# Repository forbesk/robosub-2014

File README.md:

robosub-2014
============

#Configuration

###Virtual Environment
The following steps below will setup the python virtual environment.

```bash
virtualenv env
source env/bin/activate
pip install -r requirements.txt
```

###Setting up Dashboard
The dashboard has several dependencies that need to be installed before it can be used.

__development__
```bash
pushd src/auvweb/dashboard
bower install
npm install
popd
```

__production__
```bash
pushd src/auvweb/dashboard
bower install -p
popd
```

###Development Server
Once your virtual environment has been configured and the Dashboard has its required
dependencies the following command will run the auvweb server. AUVWeb should now be running on port `5000`.

__development__
```bash
bin/auvweb
```

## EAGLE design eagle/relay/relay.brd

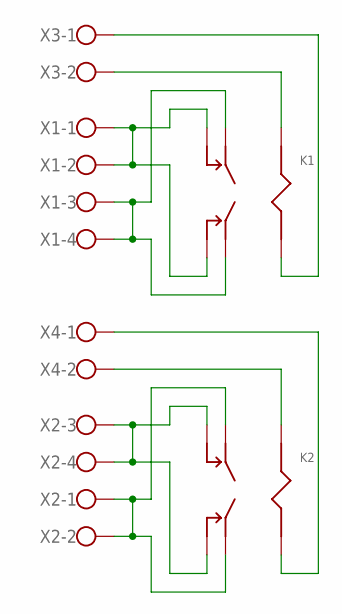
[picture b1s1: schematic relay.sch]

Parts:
K1, K2: T92S7D12; T92-PCPIN
X1, X2: W237-4
X3, X4: W237-102

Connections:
unnamed: K1.2A (2), K1.2B (2), K1.6A (6), K1.6B (6), X1.1, X1.2
unnamed: K1.4A (4), K1.4B (4), K1.8A (8), K1.8B (8), X1.3, X1.4
unnamed: K1.0A (0), K1.0B (0), X3.2
unnamed: K1.1A (1), K1.1B (1), X3.1
unnamed: K2.2A (2), K2.2B (2), K2.6A (6), K2.6B (6), X2.3, X2.4
unnamed: K2.4A (4), K2.4B (4), K2.8A (8), K2.8B (8), X2.1, X2.2
unnamed: K2.0A (0), K2.0B (0), X4.2
unnamed: K2.1A (1), K2.1B (1), X4.1

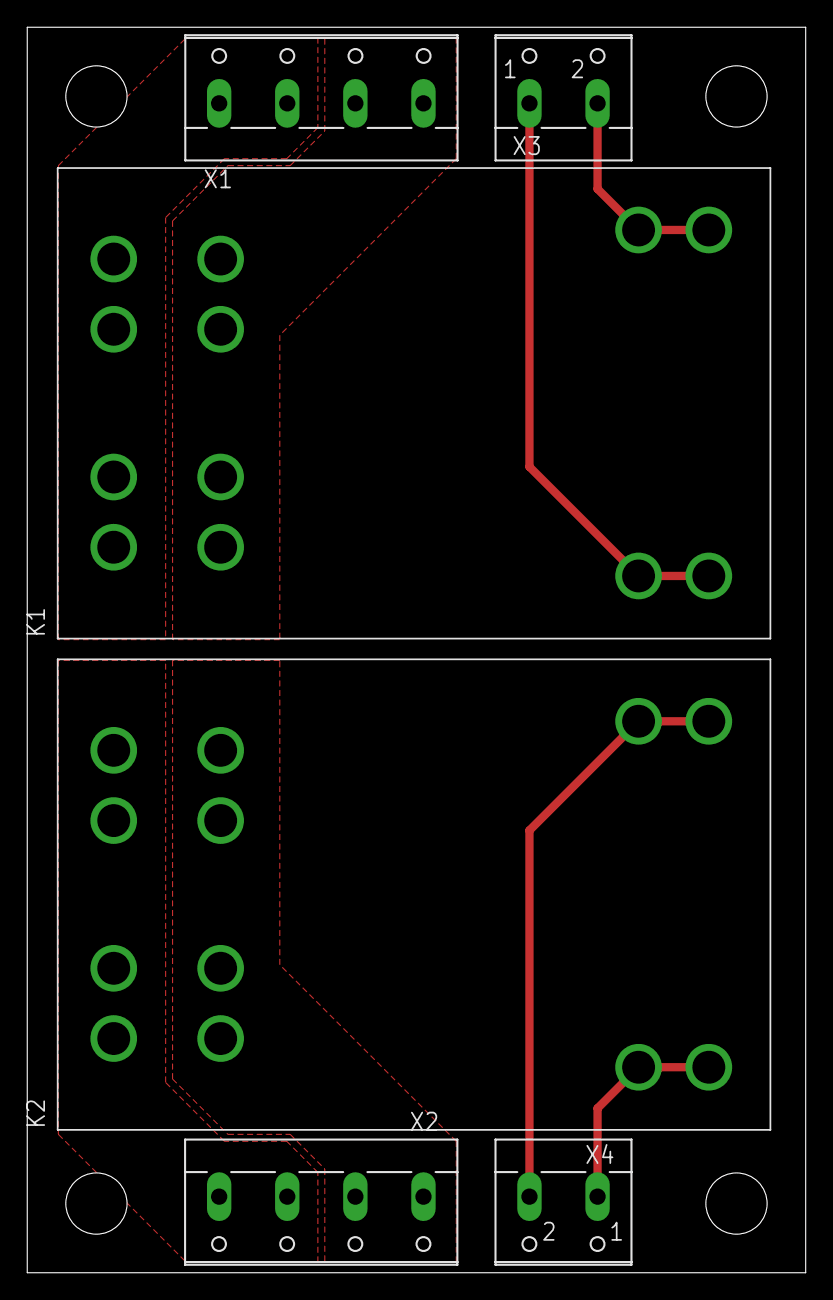
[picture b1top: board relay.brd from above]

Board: 2 copper layers, 57.1 x 91.4 mm, 6 parts (0 on the bottom side), 8 nets.

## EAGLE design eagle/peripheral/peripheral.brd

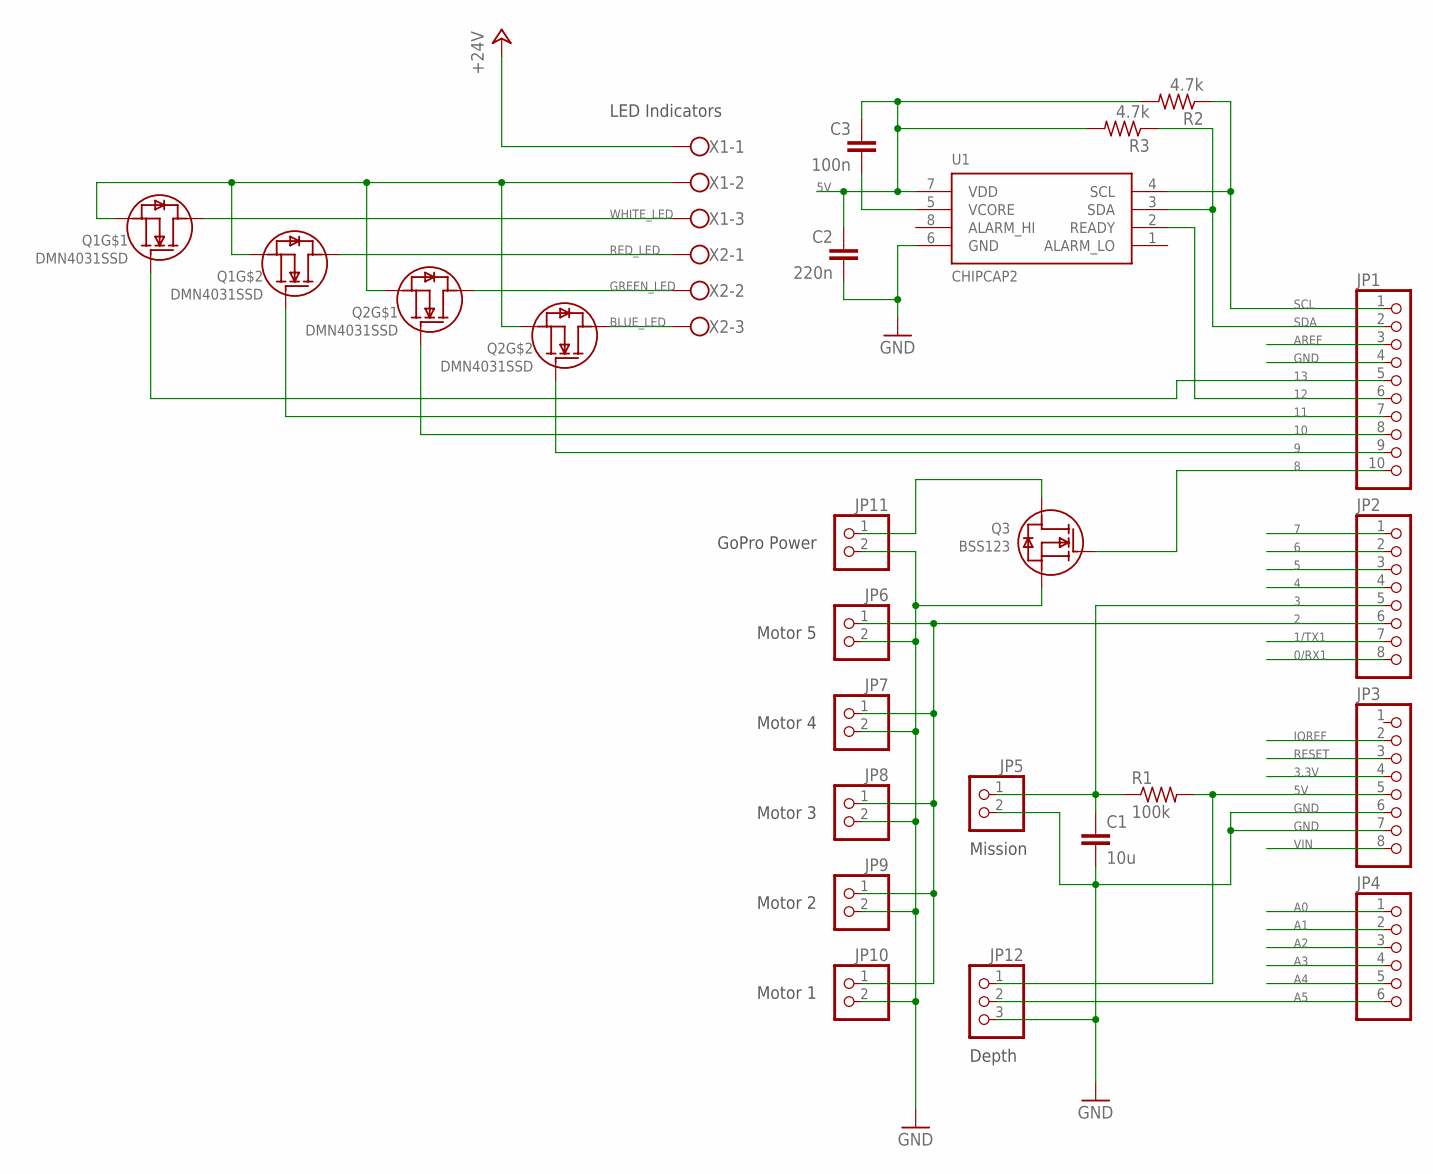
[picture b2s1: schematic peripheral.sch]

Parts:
C1: 10u; C0805K
C2: 220n; C0603
C3: 100n; C0603
JP1: PINHD-1X10; 1X10
JP2, JP3: PINHD-1X8; 1X08
JP4: PINHD-1X6; 1X06
JP5, JP6, JP7, JP8, JP9, JP10, JP11: PINHD-1X2; 1X02
JP12: PINHD-1X3; 1X03
Q1, Q2: DMN4031SSD; SO-8
Q3: BSS123; SOT-23
R1: 100k; R0805
R2, R3: 4.7k; R0603
U1: CHIPCAP2
X1, X2: W237-103

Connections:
0/RX1: JP2.8
1/TX1: JP2.7
2: JP2.6, JP6.1, JP7.1, JP8.1, JP9.1, JP10.1
3: C1.1, JP2.5, JP5.1, R1.1
3.3V: JP3.4
4: JP2.4
5: JP2.3
5V: C2.1, C3.1, JP3.5, JP12.1, R1.2, R2.2, R3.2, U1.7 (VDD)
6: JP2.2
7: JP2.1
8: JP1.10, Q3.1 (G)
9: JP1.9, Q2.2 (G)
10: JP1.8, Q2.4 (G)
11: JP1.7, Q1.2 (G)
12: JP1.6, U1.2 (READY)
13: JP1.5, Q1.4 (G)
+24V: X1.1
A0: JP4.1
A1: JP4.2
A2: JP4.3
A3: JP4.4
A4: JP4.5
A5: JP4.6, JP12.2
AREF: JP1.3
BLUE_LED: Q2.7 (D), Q2.8 (D), X2.3
GND: C1.2, C2.2, JP1.4, JP3.6, JP3.7, JP5.2, JP6.2, JP7.2, JP8.2, JP9.2, JP10.2, JP11.2, JP12.3, Q3.3 (S), U1.6 (GND)
GREEN_LED: Q2.5 (D), Q2.6 (D), X2.2
IOREF: JP3.2
unnamed: JP11.1, Q3.2 (D)
unnamed: C3.2, U1.5 (VCORE)
unnamed: Q1.1 (S), Q1.3 (S), Q2.1 (S), Q2.3 (S), X1.2
RED_LED: Q1.7 (D), Q1.8 (D), X2.1
RESET: JP3.3
SCL: JP1.1, R2.1, U1.4 (SCL)
SDA: JP1.2, R3.1, U1.3 (SDA)
VIN: JP3.8
WHITE_LED: Q1.5 (D), Q1.6 (D), X1.3

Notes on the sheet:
Motor 1
Motor 2
Motor 3
Motor 4
Motor 5
GoPro Power
Mission
Depth
LED Indicators

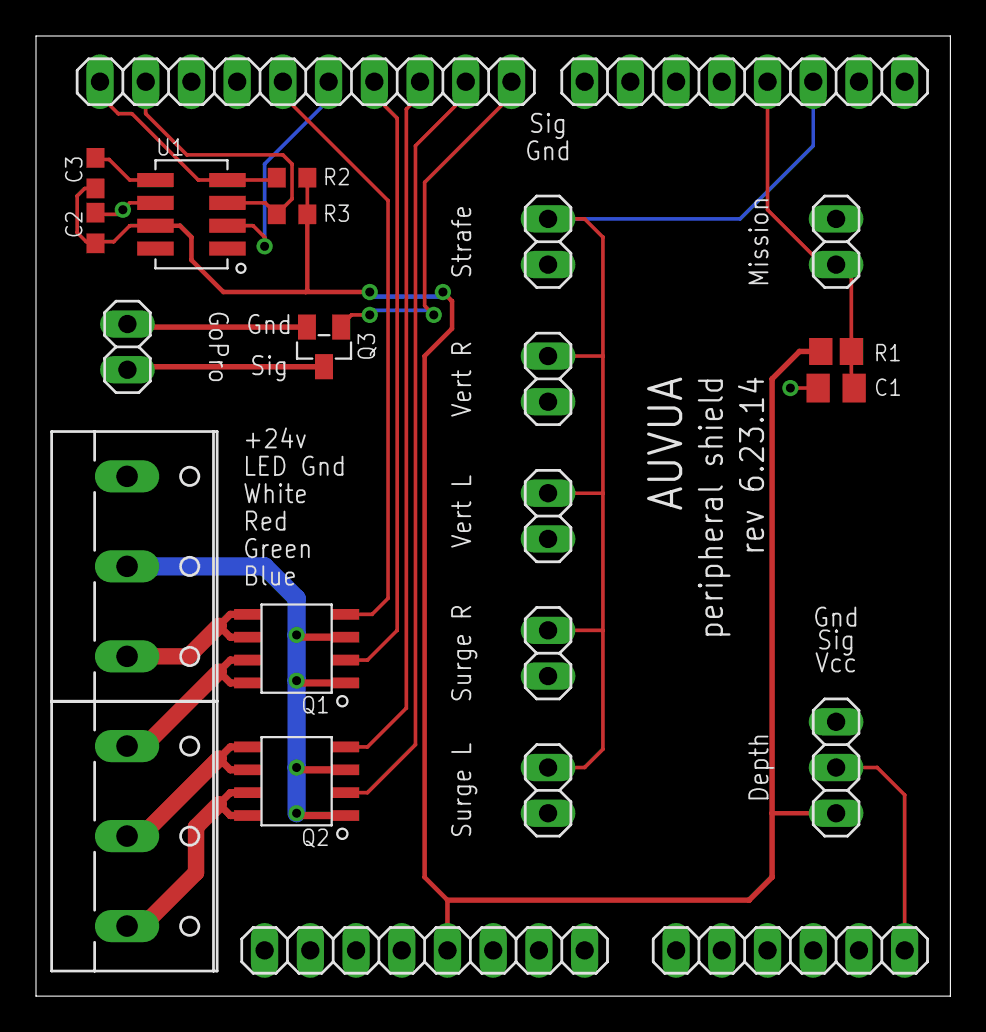
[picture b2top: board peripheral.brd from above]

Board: 2 copper layers, 50.8 x 53.3 mm, 24 parts (0 on the bottom side), 20 nets.

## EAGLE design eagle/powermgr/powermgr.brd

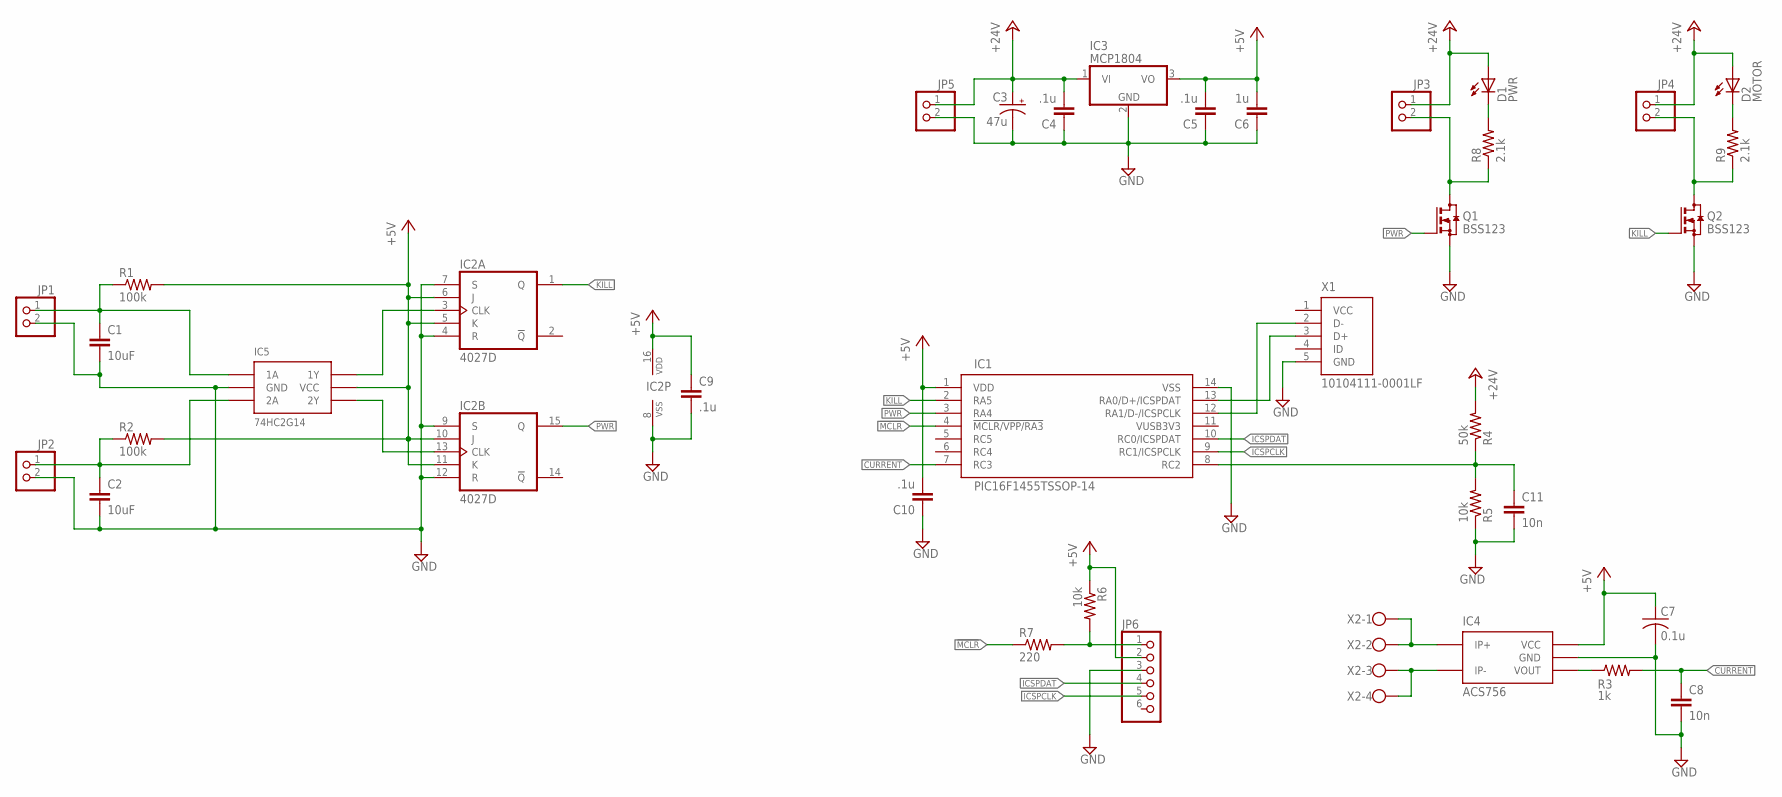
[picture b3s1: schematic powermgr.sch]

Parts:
C1, C2: 10uF; C0805
C3: 47u; E2,5-6
C4, C5: .1u; C0805
C6: 1u; C0805
C7: 0.1u; C1206K
C8, C11: 10n; C0603K
C9, C10: .1u; C0603K
D1: PWR; CHIP-LED0805
D2: MOTOR; CHIP-LED0805
IC1: PIC16F1455TSSOP-14; TSSOP-14
IC2: 4027D; SO16
IC3: MCP1804; SOT223
IC4: ACS756; 5PFF
IC5: 74HC2G14; TSSOP-6
JP1, JP2, JP3, JP4, JP5: PINHD-1X2; 1X02
JP6: PINHD-1X6; 1X06
Q1, Q2: BSS123; SOT23
R1, R2: 100k; R0805
R3: 1k; R0603
R4: 50k; R0603
R5, R6: 10k; R0603
R7: 220; R0603
R8, R9: 2.1k; R0805
X1: 10104111-0001LF; USBAB
X2: W237-4

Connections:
!MCLR: IC1.4 (!MCLR/VPP/RA3), R7.1
+5V: C5.2, C6.2, C7.1, C9.1, C10.2, IC1.1 (VDD), IC2.5 (K), IC2.6 (J), IC2.10 (J), IC2.11 (K), IC2.16 (VDD), IC3.3 (VO), IC4.1 (VCC), IC5.5 (VCC), JP6.2, R1.2, R2.2, R6.1
+24V: C3.+, C4.2, D1.A, D2.A, IC3.1 (VI), JP3.1, JP4.1, JP5.1, R4.2
CURRENT: C8.1, IC1.7 (RC3), R3.2
GND: C1.2, C2.2, C3.-, C4.1, C5.1, C6.1, C7.2, C8.2, C9.2, C10.1, C11.2, IC1.14 (VSS), IC2.4 (R), IC2.7 (S), IC2.8 (VSS), IC2.9 (S), IC2.12 (R), IC3.2 (GND), IC4.2 (GND), IC5.2 (GND), JP1.2, JP2.2, JP5.2, JP6.3, Q1.2 (S), Q2.2 (S), R5.1, X1.5 (GND)
ICSPCLK: IC1.9 (RC1/ICSPCLK), JP6.5
ICSPDAT: IC1.10 (RC0/ICSPDAT), JP6.4
KILL: IC1.2 (RA5), IC2.1 (Q), Q2.1 (G)
unnamed: C1.1, IC5.1 (1A), JP1.1, R1.1
unnamed: JP3.2, Q1.3 (D), R8.1
unnamed: JP4.2, Q2.3 (D), R9.1
unnamed: IC4.4 (IP+), X2.1, X2.2
unnamed: IC4.5 (IP-), X2.3, X2.4
unnamed: D1.C, R8.2
unnamed: IC4.3 (VOUT), R3.1
unnamed: C11.1, IC1.8 (RC2), R4.1, R5.2
unnamed: JP6.1, R6.2, R7.2
unnamed: D2.C, R9.2
unnamed: C2.1, IC5.3 (2A), JP2.1, R2.1
unnamed: IC2.3 (CLK), IC5.6 (1Y)
unnamed: IC2.13 (CLK), IC5.4 (2Y)
PWR: IC1.3 (RA4), IC2.15 (Q), Q1.1 (G)
USBD+: IC1.13 (RA0/D+/ICSPDAT), X1.3 (D+)
USBD-: IC1.12 (RA1/D-/ICSPCLK), X1.2 (D-)

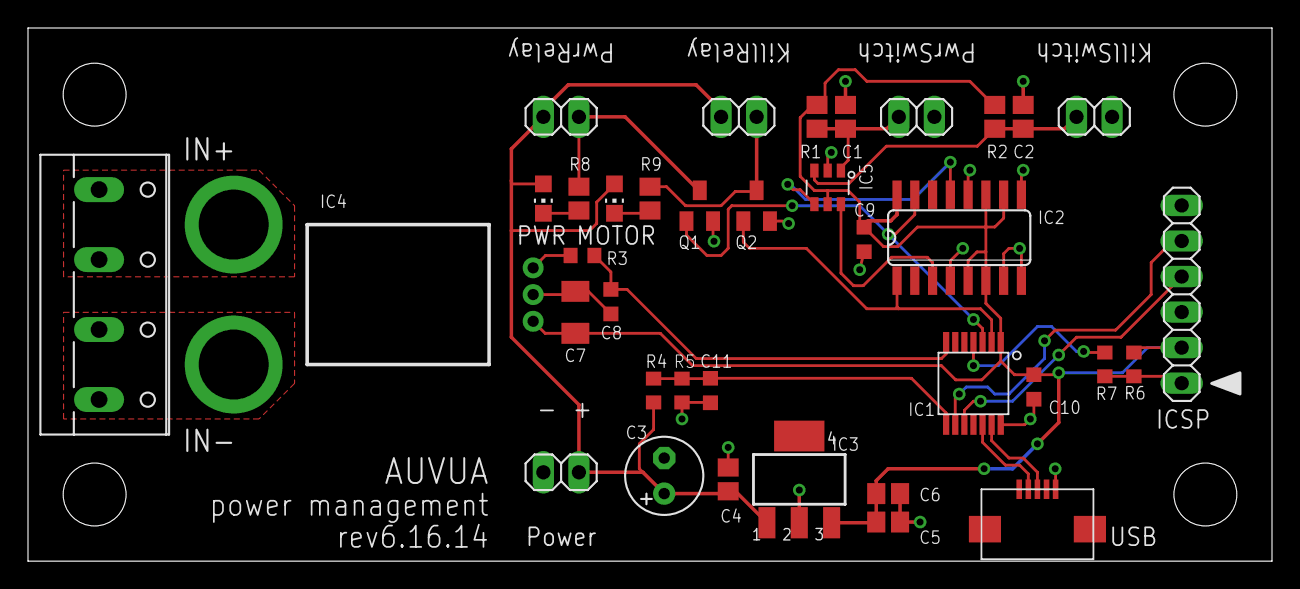
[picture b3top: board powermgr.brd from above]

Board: 2 copper layers, 88.9 x 38.1 mm, 37 parts (0 on the bottom side), 24 nets.

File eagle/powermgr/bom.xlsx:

Part | Description | Vendor | Vendor PN | Price | Quantity | Ext. Price | Notes
C1, C2 | SMD 0805 cap, 10uF | Digikey | 1276-2890-1-ND | 0.22 | 2 | 0.44
C3 | E2.5-6 polarized cap, 47uF | Digikey | 493-1106-ND | 0.28000000000000003 | 1 | 0.28000000000000003
C4, C5 | SMD 0805 cap, 0.1uF | Digikey | 1276-1003-1-ND | 0.1 | 2 | 0.2
C6 | SMD 0805 cap, 1.0uF | Digikey | 1276-1029-1-ND | 0.1 | 1 | 0.1
C7 | SMD 1206 cap, 0.1uF | Digikey | 1276-1017-1-ND | 0.1 | 1 | 0.1
C8, C11 | SMD 0603 cap, 10nF | Digikey | 1276-1921-1-ND | 0.1 | 2 | 0.2
C9, C10 | SMD 0603 cap, 0.1uF | Digikey | 1276-1857-1-ND | 0.1 | 1 | 0.1
R1, R2 | SMD 0805 res, 100k | Digikey | RMCF0805FT100KCT-ND | 0.04 | 2 | 0.08
R3 | SMD 0603 res, 1k | Digikey | RMCF0603JT1K00CT-ND | 0.02 | 1 | 0.02
R4 | SMD 0603 res, 50k | Digikey | RMCF0603JT51K0CT-ND | 0.02 | 1 | 0.02 | 51k available for $0.02, 50k is >$3
R5, R6 | SMD 0603 res, 10k | Digikey | RMCF0603JT10K0CT-ND | 0.02 | 2 | 0.04
R7 | SMD 0603 res, 220 | Digikey | RMCF0603JT220RCT-ND | 0.02 | 1 | 0.02
R8, R9 | SMD 0805 res, 2.1k | Digikey | RMCF0805FT2K10CT-ND | 0.04 | 2 | 0.08
D1, D2 | SMD 0805 green LED | Digikey | 732-4983-1-ND | 0.28999999999999998 | 2 | 0.57999999999999996
Q1, Q2 | SOT-23 N-MOSFET | Digikey | BSS123NCT-ND | 0.24 | 2 | 0.48
JP1, JP2, JP3, JP4, JP5 | 2-pin 0.1" lock header | Digikey | A1921-ND | 0.14000000000000001 | 5 | 0.70000000000000007
JP6 | 6-pin 0.1" header | Digikey | 609-3263-ND | 0.24 | 1 | 0.24
X1 | Micro-USB A/B | Digikey | 609-4053-1-ND | 0.79 | 1 | 0.79
X2 | 4-pin 5mm screw terminal | Digikey | A98357-ND | 2.71 | 1 | 2.71
IC1 | PIC16F micro controller | Digikey | PIC16F1455-I/ST-ND | 1.78 | 1 | 1.78
IC2 | 4027D dual JK flip-flop | Digikey | MC14027BDGOS-ND | 0.44 | 1 | 0.44
IC3 | 5v LDO regulator | Digikey | MCP1804T-5002I/DBCT-ND | 0.84 | 1 | 0.84
IC4 | 100A current transducer | Digikey | 620-1238-ND | 7.98 | 1 | 7.98
IC5 | Dual Schmitt Trigger | Digikey | 568-7739-1-ND | 0.52 | 1 | 0.52
 |  |  |  | Total: | 36 | 18.739999999999998

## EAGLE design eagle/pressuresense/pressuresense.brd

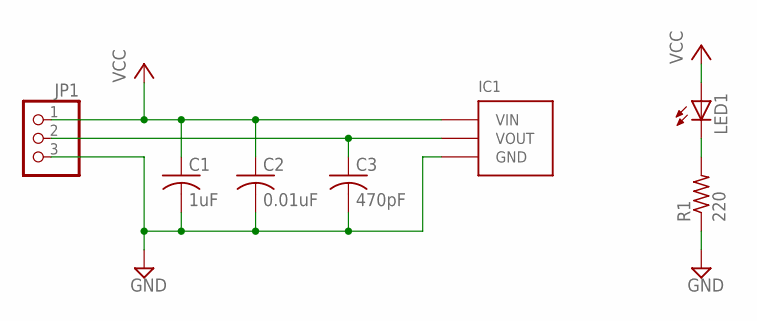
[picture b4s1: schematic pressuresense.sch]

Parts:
C1: 1uF; C0805K
C2: 0.01uF; C0805K
C3: 470pF; C0805K
IC1: MPXA4250AC6U
JP1: PINHD-1X3; 1X03
LED1: LEDCHIP-LED0805; CHIP-LED0805
R1: 220; R0805

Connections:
GND: C1.2, C2.2, C3.2, IC1.P$3 (GND), JP1.3, R1.1
unnamed: LED1.C, R1.2
VCC: C1.1, C2.1, IC1.P$2 (VIN), JP1.1, LED1.A
VOUT: C3.1, IC1.P$4 (VOUT), JP1.2

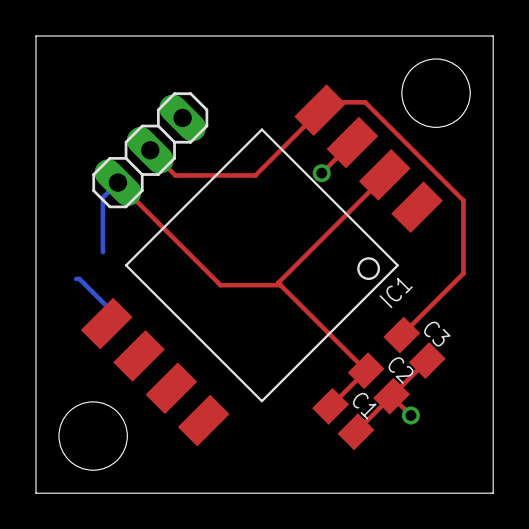
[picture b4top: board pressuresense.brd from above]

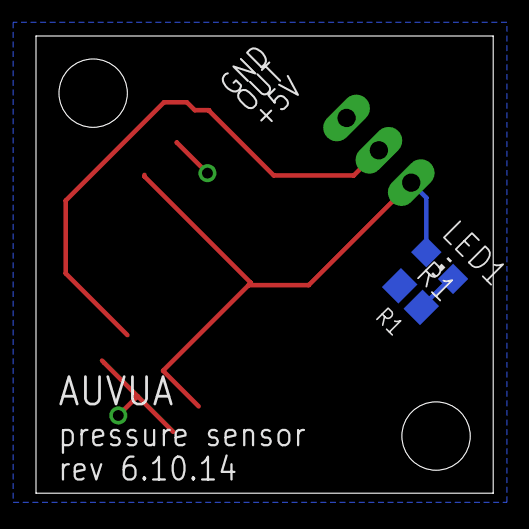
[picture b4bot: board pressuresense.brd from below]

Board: 2 copper layers, 25.4 x 25.4 mm, 7 parts (2 on the bottom side), 4 nets.

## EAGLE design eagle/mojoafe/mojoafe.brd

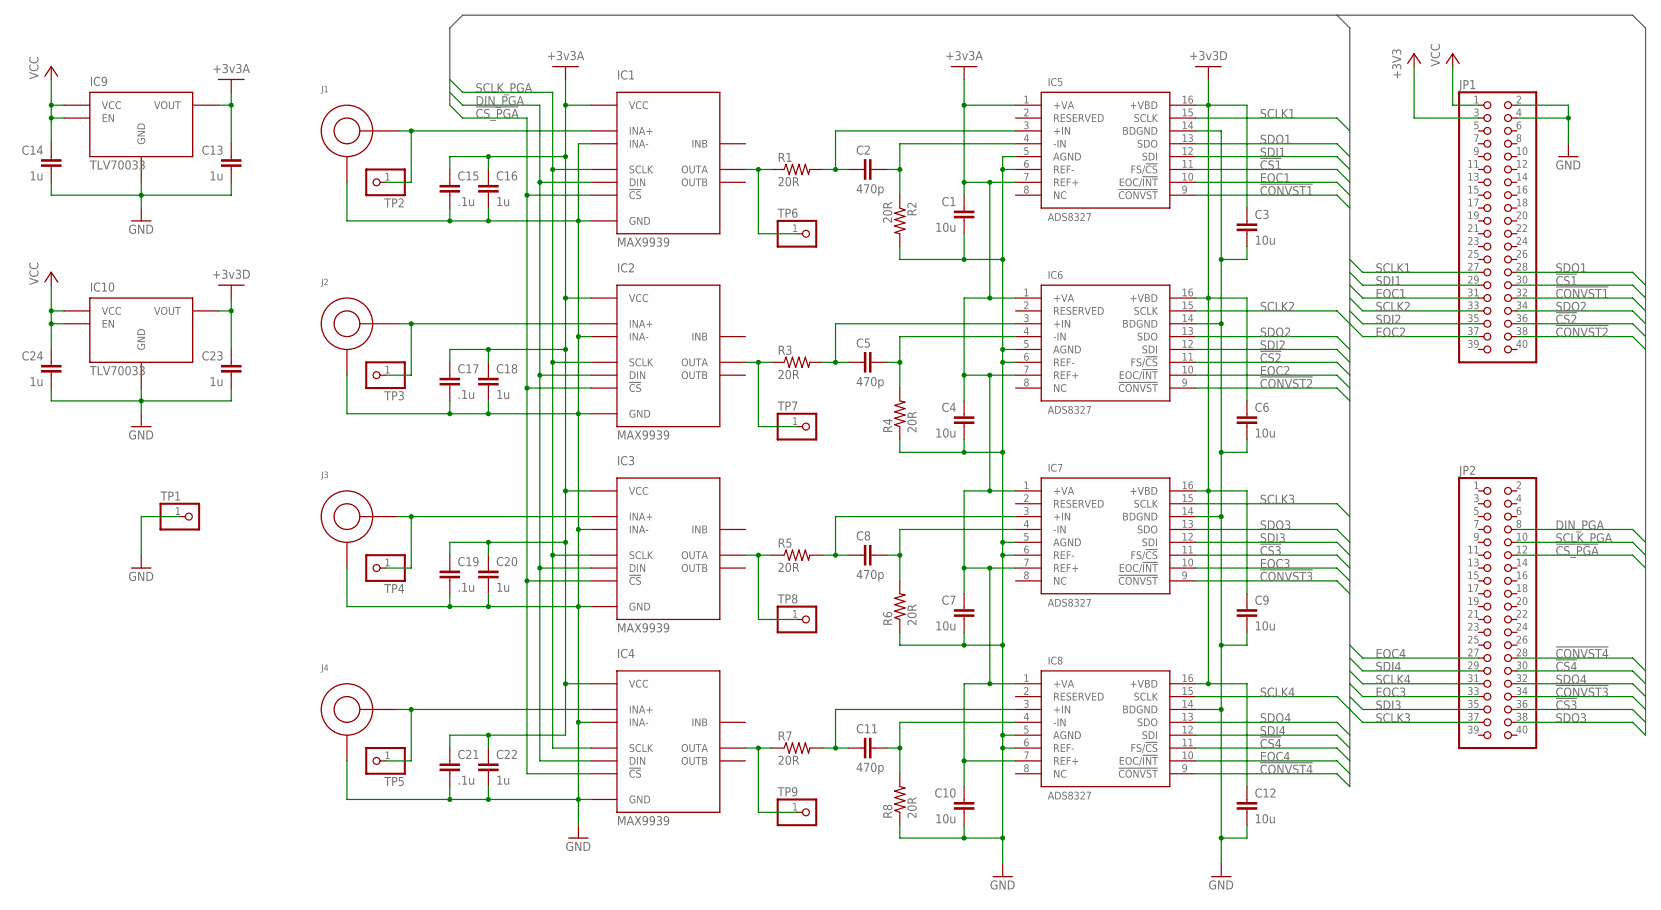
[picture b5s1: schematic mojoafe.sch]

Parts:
C1, C3, C4, C6, C7, C9, C10, C12: 10u; C0603K
C2, C5, C8, C11: 470p; C0603K
C13, C14, C16, C18, C20, C22, C23, C24: 1u; C0603K
C15, C17, C19, C21: .1u; C0603K
IC1, IC2, IC3, IC4: MAX9939; UMAX10
IC5, IC6, IC7, IC8: ADS8327; TSSOP16
IC9, IC10: TLV70033; SOT5
J1, J2, J3, J4: SMB50R
JP1, JP2: PINHD-2X20; 2X20
R1, R2, R3, R4, R5, R6, R7, R8: 20R; R0603
TP1, TP2, TP3, TP4, TP5, TP6, TP7, TP8, TP9: PINHD-1X1; 1X01

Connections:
!CONVST1: IC5.9 (!CONVST), JP1.32
!CONVST2: IC6.9 (!CONVST), JP1.38
!CONVST3: IC7.9 (!CONVST), JP2.34
!CONVST4: IC8.9 (!CONVST), JP2.28
!CS1: IC5.11 (FS/!CS), JP1.30
!CS2: IC6.11 (FS/!CS), JP1.36
!CS3: IC7.11 (FS/!CS), JP2.36
!CS4: IC8.11 (FS/!CS), JP2.30
!CS_PGA: IC1.10 (!CS), IC2.10 (!CS), IC3.10 (!CS), IC4.10 (!CS), JP2.12
+3V3: JP1.3
+3V3A: C1.1, C4.1, C7.1, C10.1, C13.1, C15.1, C16.1, C17.1, C18.1, C19.1, C20.1, C21.1, C22.1, IC1.9 (VCC), IC2.9 (VCC), IC3.9 (VCC), IC4.9 (VCC), IC5.1 (+VA), IC5.7 (REF+), IC6.1 (+VA), IC6.7 (REF+), IC7.1 (+VA), IC7.7 (REF+), IC8.1 (+VA), IC8.7 (REF+), IC9.5 (VOUT)
+3V3D: C3.1, C6.1, C9.1, C12.1, C23.1, IC5.16 (+VBD), IC6.16 (+VBD), IC7.16 (+VBD), IC8.16 (+VBD), IC10.5 (VOUT)
DIN_PGA: IC1.2 (DIN), IC2.2 (DIN), IC3.2 (DIN), IC4.2 (DIN), JP2.8
EOC1: IC5.10 (EOC/!INT), JP1.31
EOC2: IC6.10 (EOC/!INT), JP1.37
EOC3: IC7.10 (EOC/!INT), JP2.33
EOC4: IC8.10 (EOC/!INT), JP2.27
GND: C1.2, C3.2, C4.2, C6.2, C7.2, C9.2, C10.2, C12.2, C13.2, C14.2, C15.2, C16.2, C17.2, C18.2, C19.2, C20.2, C21.2, C22.2, C23.2, C24.2, IC1.3 (GND), IC1.4 (INA-), IC2.3 (GND), IC2.4 (INA-), IC3.3 (GND), IC3.4 (INA-), IC4.3 (GND), IC4.4 (INA-), IC5.5 (AGND), IC5.6 (REF-), IC5.14 (BDGND), IC6.5 (AGND), IC6.6 (REF-), IC6.14 (BDGND), IC7.5 (AGND), IC7.6 (REF-), IC7.14 (BDGND), IC8.5 (AGND), IC8.6 (REF-), IC8.14 (BDGND), IC9.2 (GND), IC10.2 (GND), J1.P$1 (1), J1.P$2 (1), J1.P$3 (1), J1.P$4 (1), J2.P$1 (1), J2.P$2 (1), J2.P$3 (1), J2.P$4 (1), J3.P$1 (1), J3.P$2 (1), J3.P$3 (1), J3.P$4 (1), J4.P$1 (1), J4.P$2 (1), J4.P$3 (1), J4.P$4 (1), JP1.2, JP1.4, R2.2, R4.1, R6.1, R8.1, TP1.1
unnamed: IC1.5 (INA+), J1.P$5 (2), TP2.1
unnamed: IC3.8 (OUTA), R5.1, TP8.1
unnamed: C8.2, IC7.4 (-IN), R6.2
unnamed: IC2.5 (INA+), J2.P$5 (2), TP3.1
unnamed: IC3.5 (INA+), J3.P$5 (2), TP4.1
unnamed: IC4.8 (OUTA), R7.1, TP9.1
unnamed: IC1.8 (OUTA), R1.1, TP6.1
unnamed: IC2.8 (OUTA), R3.1, TP7.1
unnamed: C5.1, IC6.3 (+IN), R3.2
unnamed: C2.1, IC5.3 (+IN), R1.2
unnamed: C5.2, IC6.4 (-IN), R4.2
unnamed: C2.2, IC5.4 (-IN), R2.1
unnamed: C8.1, IC7.3 (+IN), R5.2
unnamed: IC4.5 (INA+), J4.P$5 (2), TP5.1
unnamed: C11.1, IC8.3 (+IN), R7.2
unnamed: C11.2, IC8.4 (-IN), R8.2
SCLK1: IC5.15 (SCLK), JP1.27
SCLK2: IC6.15 (SCLK), JP1.33
SCLK3: IC7.15 (SCLK), JP2.37
SCLK4: IC8.15 (SCLK), JP2.31
SCLK_PGA: IC1.1 (SCLK), IC2.1 (SCLK), IC3.1 (SCLK), IC4.1 (SCLK), JP2.10
SDI1: IC5.12 (SDI), JP1.29
SDI2: IC6.12 (SDI), JP1.35
SDI3: IC7.12 (SDI), JP2.35
SDI4: IC8.12 (SDI), JP2.29
SDO1: IC5.13 (SDO), JP1.28
SDO2: IC6.13 (SDO), JP1.34
SDO3: IC7.13 (SDO), JP2.38
SDO4: IC8.13 (SDO), JP2.32
VCC: C14.1, C24.1, IC9.1 (VCC), IC9.3 (EN), IC10.1 (VCC), IC10.3 (EN), JP1.1

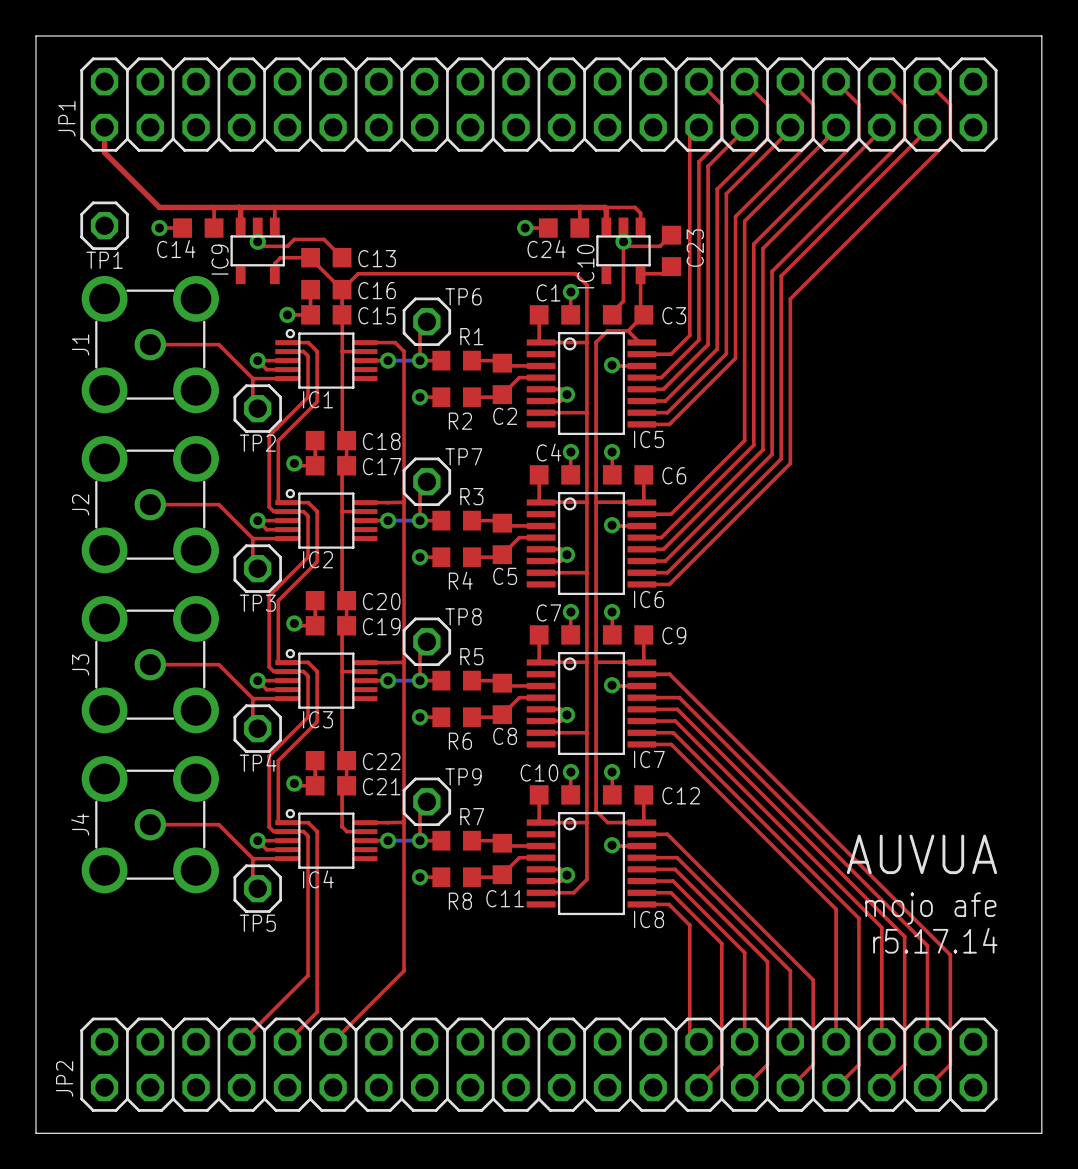
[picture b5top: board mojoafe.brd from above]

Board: 2 copper layers, 55.9 x 61.0 mm, 57 parts (0 on the bottom side), 47 nets.

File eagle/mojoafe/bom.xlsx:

Part | Description | Vendor | Vendor PN | Price | Quantity | Ext. Price | Comments
IC1, IC2, IC3, IC4 | Differential PGA | Digikey | MAX9939AUB+-ND | 1.68 | 4 | 6.72
IC5, IC6, IC7, IC8 | 500ksps 16-bit ADC | Digikey | 296-19764-ND | 13.07 | 4 | 52.28
IC9, IC10 | 3.3v LDO Regulator | Digikey | 296-27937-1-ND | 0.51 | 2 | 1.02
J1, J2, J3, J4 | SMB Jack 50 ohm straight | Digikey | J614-ND | 2.06 | 4 | 8.24 | Mating plug: J466-ND
JP1, JP2 | 40pos 2row 0.1" header, male | Digikey | S2012EC-20-ND | 0.71 | 2 | 1.42
TP1, TP2, TP3, TP4, TP5, TP6, TP7, TP8, TP9 | 0.04" loop test point | Digikey | 5001K-ND | 0.34 | 9 | 3.06
R1, R2, R3, R4, R5, R6, R7, R8 | 20ohm 0603-SMD 1% resistor | Digikey | RMCF0603FT20R0CT-ND | 0.04 | 8 | 0.32
C1, C3, C4, C6, C7, C9, C10, C12 | 10uF 0603-SMD 10% capacitor | Digikey | 1276-1192-1-ND | 0.48 | 8 | 3.84
C2, C5, C8, C11 | 470pF 0603-SMD 5% capacitor | Digikey | 490-6363-1-ND | 0.1 | 4 | 0.4
C15, C17, C19, C21 | 0.1uF 0603-SMD 5% capacitor | Digikey | 1276-1929-1-ND | 0.12 | 4 | 0.48
C13, C14, C16, C18, C20, C22, C23, C24 | 1uF 0603-SMD 10% capacitor | Digikey | 490-3897-1-ND | 0.1 | 8 | 0.8
 |  |  |  |  | Total | 78.580000000000013

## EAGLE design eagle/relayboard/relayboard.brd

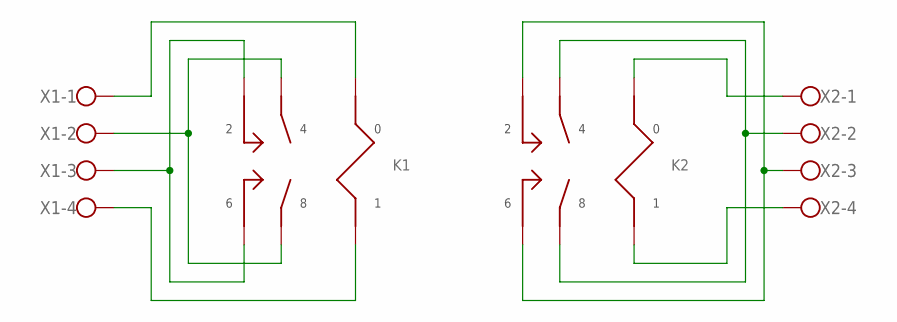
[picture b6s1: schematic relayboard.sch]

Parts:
K1, K2: T92S7D12-24; T92
X1, X2: W237-4

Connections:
unnamed: K1.P$9, K1.P$10, X1.1
unnamed: K1.P$11, K1.P$12, X1.4
unnamed: K1.P$1, K1.P$2, K1.P$5, K1.P$6, X1.3
unnamed: K1.P$3, K1.P$4, K1.P$7, K1.P$8, X1.2
unnamed: K2.P$9, K2.P$10, X2.1
unnamed: K2.P$11, K2.P$12, X2.4
unnamed: K2.P$3, K2.P$4, K2.P$7, K2.P$8, X2.2
unnamed: K2.P$1, K2.P$2, K2.P$5, K2.P$6, X2.3

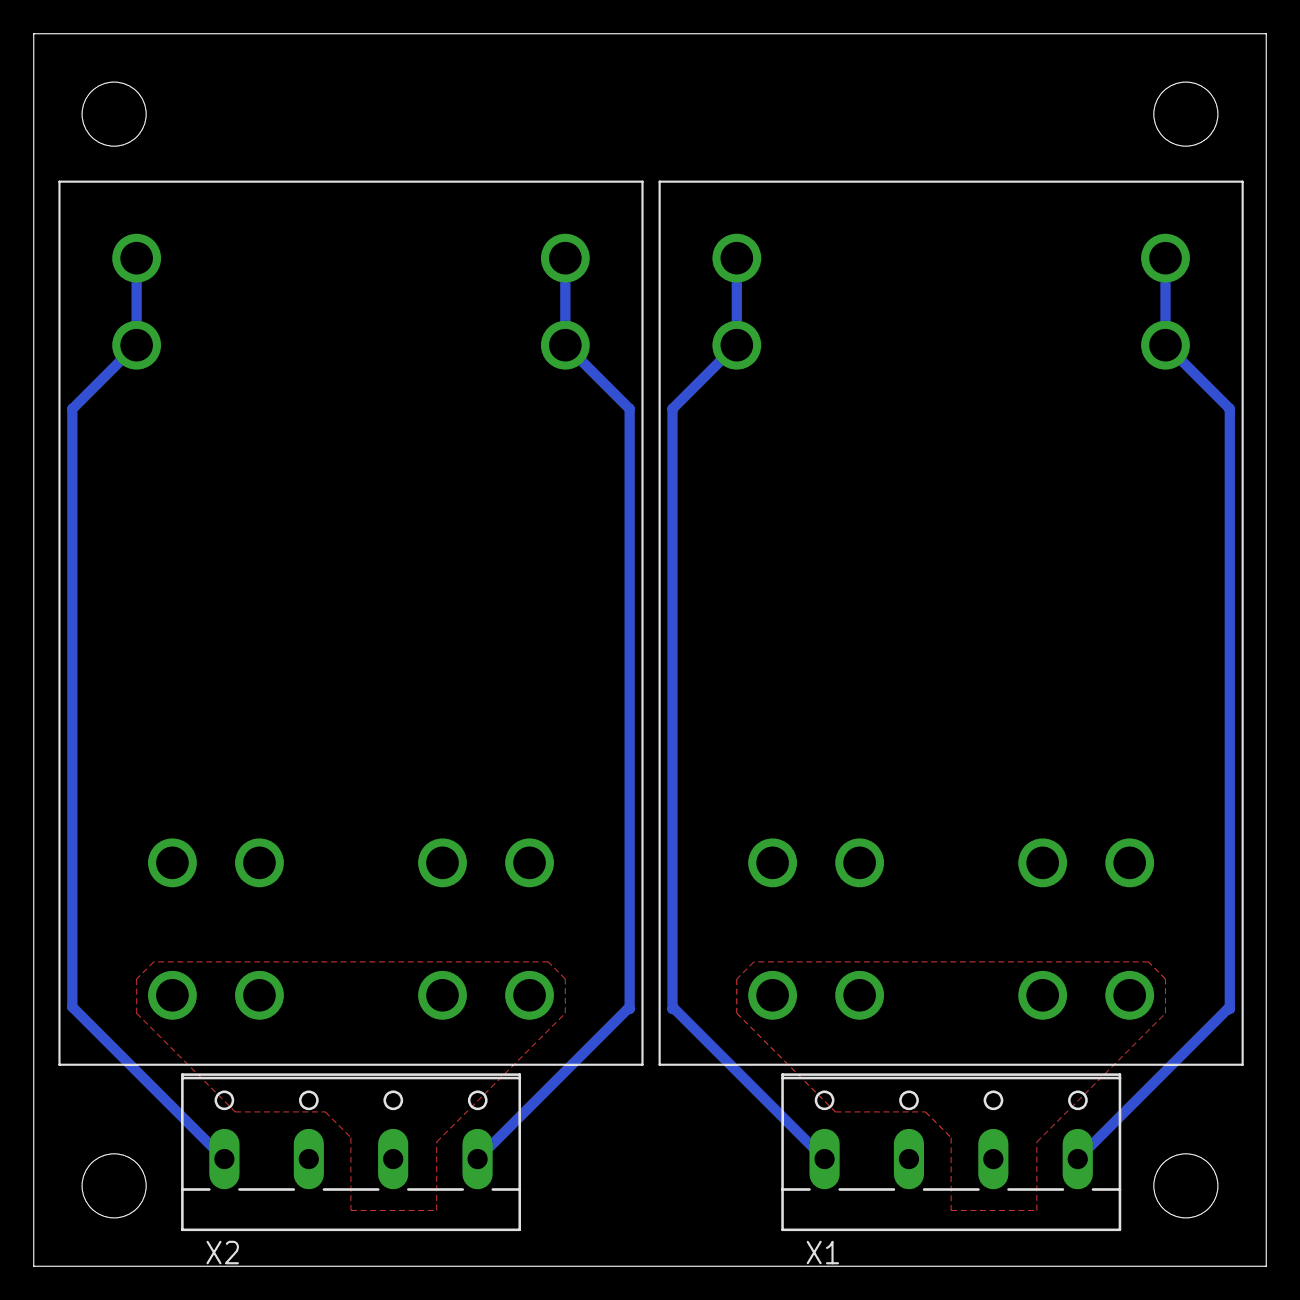
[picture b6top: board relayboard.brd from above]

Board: 2 copper layers, 73.0 x 73.0 mm, 4 parts (0 on the bottom side), 8 nets.

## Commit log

2014-04-10 initial auvweb client commit
    Setup the initial framework for the web application. The dashboard has
    an initial dependency on Backbone and React. The backend runs on Flask
    and has an api blueprint for communicating with the agent daemon. A
    secondary dashboard blueprint serves all static content for the
    dashboard.
2014-04-10 update README with dashboard configure
    modified: README.md
2014-04-10 add missing requirements.txt new file: requirements.txt
2014-04-10 fix route name to redirect to /dashboard
2014-04-22 Added EAGLE PCB projects.
2014-04-29 Added eclipse project files for AUV control
2014-04-29 l2git
2014-04-29 progress on mojo analog front-end
2014-04-29 cleaned up /auvweb bin
2014-05-07 finished mojo afe PCB, generated CAM files and BoM
2014-05-11 rev 5.7.14 complete, sent for production
2014-05-21 Widened board to properly fit Mojo. Rev 5.17.14 sent for prodution.
2014-05-21 Dev branch
2014-05-21 Adding files
2014-05-21 Adding packages and hardware class abstractions
2014-05-24 basic task framework
2014-05-24 added entry point Server
2014-05-24 Sample task added, model functionality started
2014-05-24 It appears to be working
2014-06-04 added glassfish 4 server (jre1.7 req) & tyrus websocket endpoints
2014-06-07 Added JSON websocket output to dashboard endpoint
2014-06-07 Added static page for testing dashboard websocket
2014-06-09 First pass of power management board completed
2014-06-09 Added LEDs, finalized silkscreen
2014-06-09 Performed DRC, moved vias. Completed DRC.
2014-06-10 Finalized power management board. Sent rev 6.10.14 for production.
2014-06-11 Finalized pressure sensor board. Sent rev 6.10.14 for production.
2014-06-11 Removed relayboard
2014-06-17 Added schmitt trigger to switch inputs. Sent rev 6.16.14 for production.
2014-06-19 Added empty project for peripheral board (arduino shield)
2014-06-20 Added power management board bill of materials
2014-06-22 Added relay board to simplify mounting. No silk, barebones @ advanced
2014-06-23 Completed peripheral design layout.
2014-06-23 Generated gerber files for rev 6.23.14
2014-06-23 Zipped GTL, GBL, & drill files
2014-07-19 Restructured project, added several other files.
2014-07-19 ignore intellji project files
    modified: .gitignore
2014-07-20 restructure dashboard remove flask
    Remove the Flask web framework from the dashboard. The dashboard will
    connect to the backend using websockets.
    modified: ../.gitignore
    deleted: ../auvweb/src/__init__.py
    deleted: ../auvweb/src/api/__init__.py
    deleted: ../auvweb/src/api/devices.py
2014-07-20 Added some controllers
2014-07-20 Forgot to add the files lol
2014-07-20 refactor header to browserify and JSX
    modified: package.json
    modified: src/js/components/application.js
    modified: src/js/components/header.js
2014-07-20 add gulp task for css concatenation
    Switch to using a bundle output css file.
    modified: gulpfile.js
    modified: package.json
    modified: src/index.html
2014-07-20 port Footer components browserify and JSX
    modified: dashboard/src/js/components/application.js
    modified: dashboard/src/js/components/footer.js
2014-07-20 port Telemetry component to browserify and JSX
    modified: dashboard/src/js/components/telemetry.js
2014-07-20 add Telemetry component to Application
    modified: src/js/components/application.js
    modified: src/js/components/telemetry.js
2014-07-20 add base dispatcher
    modified: package.json
    new file: src/js/dispatchers/dispatcher.js
2014-07-20 refactor telemetry smaller components
    Split Telemetry into smaller components TelemetryInfo, MissionInfo and
    CameraPane.
    modified: application.js
    new file: camera-pane.js
    new file: mission-info.js
    new file: telemetry-info.js
2014-07-20 remove old auvweb folder
    deleted: src/auvweb/__init__.py
    deleted: src/auvweb/api/__init__.py
    deleted: src/auvweb/api/devices.py
2014-07-20 Hardware interface working. Autonomous scripting and control loops working.
2014-07-20 Initial hardware interface working
2014-07-20 Fixed hardware race condition
2014-07-21 Added depth and mission feedback. Tested controllers.
2014-07-28 Vision working with motor feedback! Also cleaned up a bunch of stuff.
2014-08-12 Competition code (-videos), 8/3/14
2015-04-17 Small cleanup, more needed
2015-04-17 Additional logging features, simplified dependencies.
